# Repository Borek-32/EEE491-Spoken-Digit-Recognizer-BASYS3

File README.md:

# FPGA MFCC digit recognizer

This repository is the source-and-evidence release of an EEE491 fixed-point
spoken-digit recognizer for the Digilent Basys 3. The design acquires an
external ADC stream and implements the full feature/classification path in
VHDL:

```text
ADC/VAD -> Hann window -> 512-point FFT -> 32-channel Mel bank
        -> log2 approximation -> 8-coefficient DCT -> template comparator
```

The packaged hardware profile is the home-fabricated microphone/ADC board on
Pmod JC. `constraints/jc_homefab.xdc` is the only top-level constraint file in
the release. Generated Vivado projects, checkpoints, bitstreams, logs and
waveform databases are deliberately not versioned.

## What is here

- `rtl/`: the eleven synthesizable VHDL units, with `top_module` as top.
- `testbench/` and `verification/`: eleven VHDL benches, retained fixed-point
  inputs/outputs, MATLAB cross-checks, and a bounded safe regression runner.
- `ip/` and `data/`: twenty AMD IP configuration files and five ROM
  initialization sources. Generated IP products are intentionally absent.
- `constraints/jc_homefab.xdc`: the complete 39-port Basys 3/JC pin profile.
- `hardware/homefab_mic_adc_pcb/`: KiCad sources, photos, verification tools,
  and report figures for the physical microphone/ADC board.
- `hardware/pcb_adc_uart/`: the isolated ADC-to-UART diagnostic and its
  explicitly bounded evidence.
- `implementation/`: retained text reports from the historical main
  run and the final JC-mapped implementation. These reports are evidence, not
  inputs to the clean build.
- `docs/report/EEE491_MFCC_Final_Report_2026-08-20.pdf`: the final project
  report.

## Quick start

Vivado 2025.2 is the reference version. Choose fresh directories outside this
repository; the scripts reject in-tree or pre-existing output directories.
Run Vivado itself from a fresh external runtime directory so journals, logs and
`.Xil` process state never enter the checkout.

```bash
repo_root=$(pwd -P)
build_dir=$(readlink -m ../mfcc-build-v1.0.0)
results_dir=$(readlink -m ../mfcc-results-v1.0.0)
runtime_dir=$(readlink -m ../mfcc-runtime-v1.0.0)
mkdir -- "$runtime_dir"

(
  cd "$runtime_dir"
  vivado -mode batch -notrace \
    -journal "$runtime_dir/01-recreate.jou" \
    -log "$runtime_dir/01-recreate.log" \
    -source "$repo_root/scripts/recreate_project.tcl" \
    -tclargs "$build_dir"

  vivado -mode batch -notrace \
    -journal "$runtime_dir/04-build-jc.jou" \
    -log "$runtime_dir/04-build-jc.log" \
    -source "$repo_root/scripts/build_jc_homefab.tcl" \
    -tclargs "$build_dir" "$results_dir" 4
)
```

The first command copies the release inputs into the external build directory,
creates a new project for `xc7a35tcpg236-1`, and regenerates IP products there.
The second runs synthesis and implementation, validates timing/routing/DRC and
the complete package-pin map, then places reports and a generated bitstream in
the external results directory.

Run the repository integrity and privacy gate with:

```bash
python3 scripts/check_release.py
```

The gate also requires Git's clean-filtered bytes to match the worktree bytes,
so a commit and fresh checkout cannot silently invalidate `SHA256SUMS`.

Or run the complete non-hardware release workflow in fresh external directories:

```bash
scripts/run_release_checks.sh ../mfcc-build-v1.0.0 \
  ../mfcc-results-v1.0.0 --top-smoke --jobs 4
```

`VIVADO_BIN` and `MATLAB_BIN` may name alternate executables. The wrapper runs
the integrity gate, recreation, nine safe XSim benches, optional top smoke,
MATLAB gates, and the full JC build. It creates the fresh external
`../mfcc-results-v1.0.0.runtime/` directory for Vivado process state and never
programs hardware. The MATLAB gate is serialized and refuses to start while
another MATLAB process is active.

See [REPRODUCIBILITY.md](REPRODUCIBILITY.md) for simulation, MATLAB, KiCad and
hardware procedures.

## Verified result and evidence boundary

The retained final JC implementation reports:

- routed setup slack `+0.671 ns` and hold slack `+0.020 ns`;
- 12,824/12,824 routable nets complete, with zero routing errors;
- zero DRC errors, critical warnings, or warnings (11 advisories);
- 5,603 LUTs, 8,437 registers, 23.5 BRAM tiles, and 15 DSPs.

Those are internal FPGA implementation results. The methodology report retains
36 `TIMING-18` warnings because external I/O delays were not characterized;
the ADC board interface is therefore not claimed as board-level timing closed.

The report describes a working bench demonstration and historical recognition
observations. No pre-labeled live session made with the final FFT/Mel-corrected
image was retained, so this release makes no numerical live-accuracy claim.
The earlier 30/30 development set predates those final corrections and is not
presented as final-system accuracy. Photographs show construction and operation;
they do not independently establish recognition accuracy.

The isolated ADC/UART reconstruction closes its declared internal timing, but
its retained CDC report contains 133 `CDC-1` critical findings, 12 `CDC-15`
warnings, and four `CDC-3` informational findings. Its corrected SPI-alignment
candidate passes simulation and implementation; the decisive voltage/UART
endpoint capture remains **NOT RUN**. These boundaries are preserved in the
corresponding hardware documentation.

## Hardware safety and explicit target selection

No script selects a programmer or serial port by a repository-embedded device
identifier. Programming requires both an explicit bitstream path and an
explicit JTAG target substring and the expected bitstream SHA-256. MATLAB
capture requires an explicit UART port, JTAG target identity, bitstream path,
expected SHA-256, programming-log path, and output path.
Inspect the discovered target and wiring before acting; a generated bitstream
or a successful JTAG configuration is not proof of correct analog behavior.

## License and citation

Original source and hardware-design files are released under the MIT License;
portfolio media, the report, retained evidence, and third-party tool/IP
material have the narrower terms described in [NOTICE.md](NOTICE.md). Citation
metadata is in [CITATION.cff](CITATION.cff).

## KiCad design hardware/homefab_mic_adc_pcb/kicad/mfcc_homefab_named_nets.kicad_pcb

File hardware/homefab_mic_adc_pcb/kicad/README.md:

# Reconciled KiCad source

This directory contains the report-ready schematic and the recovered PCB with
every routed copper island assigned its schematic net name; the one physically
isolated, unused Pmod pad is explicitly retained as `<no net>`.

- `mfcc_homefab_named_nets.kicad_sch`: schematic with the ADC ground joined to
  the existing global `GND` net.
- `mfcc_homefab_named_nets.kicad_pcb`: original board geometry with net names
  added to all pads, routed segments, and vias.
- `mfcc_homefab_named_nets.kicad_pro`: KiCad project settings generated for the
  reconciled pair.
- `tools/`: fail-closed reconstruction and verification scripts.
- `evidence/`: exported netlist, IPC-D-356 netlist, native KiCad checks,
  hashes, and the inspected schematic render.

The pre-reconciliation source copies are retained under `originals/`. Their
SHA-256 values are:

- schematic: `e35c51a3030d64c75fbf8b99cae6bb0e8106192cca6c8ed2968b3d3029f0215c`
- PCB: `d63a80d06c6ad783caed415275df6e86c6c870cf5f2c0cff97cd489689012f88`

## Exact net reconciliation

KiCad 10.0.3 native connectivity found 22 physical copper islands. Twenty-one
use the exact exported schematic names; the remaining island is an intentionally
isolated Pmod pad and remains `<no net>`.

| Island | Exact net | Pads | Segments | Vias |
| --- | --- | ---: | ---: | ---: |
| I001 | `/ref` | 4 | 12 | 0 |
| I002 | `/3v3` | 4 | 26 | 3 |
| I003 | `/JC9` | 2 | 33 | 4 |
| I004 | `GND` | 12 | 50 | 3 |
| I005 | `<no net>` | 1 | 0 | 0 |
| I006 | `/JC4` | 3 | 9 | 2 |
| I007 | `VCC` | 5 | 33 | 2 |
| I008 | `/JC3` | 2 | 4 | 1 |
| I009 | `/filter-out` | 4 | 13 | 1 |
| I010 | `/div-ref` | 4 | 14 | 0 |
| I011 | `/mic` | 3 | 15 | 2 |
| I012 | `/ss2r` | 3 | 6 | 0 |
| I013 | `/div-out` | 3 | 8 | 0 |
| I014 | `/ss2c` | 3 | 8 | 0 |
| I015 | `/amp1` | 3 | 10 | 0 |
| I016 | `/pot1` | 2 | 6 | 0 |
| I017 | `/ss1c` | 3 | 8 | 0 |
| I018 | `/ss1o` | 4 | 10 | 0 |
| I019 | `/amp2` | 2 | 7 | 0 |
| I020 | `/amp-out` | 3 | 4 | 0 |
| I021 | `/ss1r` | 3 | 8 | 0 |
| I022 | `/pot2` | 2 | 3 | 0 |

The exported schematic contains exactly these 21 named nets, and the named PCB
contains the same 21-name set. Coverage is complete: 75 pads, 287 track
segments, and 18 vias are accounted for. The before/after structured geometry
fingerprints are identical.

## Home-fabrication mirror

The successful physical board is mirrored relative to the logical pad numbers
in the recovered footprints. Net assignment therefore follows the working
electrical pins, not the printed geometric pad numbers.

ADC footprint geometry maps to the
[TI ADC121S101 pinout](https://www.ti.com/lit/ds/symlink/adc121s101.pdf)
as follows:

| Geometric pad | Actual ADC pin/function | Net |
| ---: | --- | --- |
| 1 | 3, `VIN` | `/ref` |
| 2 | 2, `GND` | `GND` |
| 3 | 1, `VA` | `/3v3` |
| 4 | 6, `/CS` | `/JC9` |
| 5 | 5, `SDATA` | `/JC4` |
| 6 | 4, `SCLK` | `/JC3` |

For the SO-14 LM324, the actual lead is `15 - geometric pad`. This places the
actual positive supply on geometric pad 11 (`VCC`) and the actual negative
supply on geometric pad 4 (`GND`), and it resolves all four amplifier stages.
The two recovered board diode references are also reversed by role relative to
the schematic; the net assignment follows the electrical clamp nodes.

## Ground correction

The source schematic used both the global `GND` net and a local `/gnd` label
for the ADC. The fabricated PCB has one common ground island. The reconciled
schematic therefore replaces only that local label with a wired global GND
symbol. It now exports one `GND` net and no `/gnd` or anonymous ADC-ground net.

## Verification boundary

`evidence/bundle_validation.json` records `PASS_NET_ASSIGNMENT`:

- 21/21 schematic names equal 21/21 named PCB nets;
- all pads, tracks, and vias are assigned to their native KiCad island;
- one isolated Pmod pad is deliberately left no-net;
- no board geometry changed;
- KiCad DRC reports zero unconnected items.

This does **not** make the legacy home-fabrication layout DRC-clean. The retained
DRC contains 126 inherited findings: 12 errors and 114 warnings, including two
copper-clearance findings, malformed/co-located Pmod holes, courtyard overlaps,
a missing formal `Edge.Cuts` outline, and dangling legacy stubs. The schematic
ERC retains 28 pre-existing structural findings (8 errors and 20 warnings),
principally because the drawing models four op-amp triangles as separate
references rather than one multi-unit LM324 package and omits connector/power
driver detail. These limitations are preserved rather than hidden.

The direct Pmod footprint also joins the geometric contacts corresponding to
JC4 and JC10. The full FPGA design still drives JC10 as a separate `pmod`
output, so that contact must remain physically unpopulated/isolated or the FPGA
constraint must be disabled before treating a future revision as fab-ready.

## Reproduce the checks

Run the net assignment with KiCad's Python runtime:

```bash
flatpak run --command=python3 org.kicad.KiCad \
  tools/assign_schematic_nets.py SOURCE.kicad_pcb OUTPUT.kicad_pcb \
  --manifest evidence/net_assignment_manifest.json
```

Then export the schematic netlist/ERC and PCB DRC with `kicad-cli`, and run:

```bash
python3 tools/verify_named_bundle.py . \
  --desktop-schematic originals/mfcc.kicad_sch \
  --desktop-board originals/mfccsmd.kicad_pcb \
  --output evidence/bundle_validation.json
```

`PASS_NET_ASSIGNMENT` is deliberately narrower than fabrication approval. The
retained 126 PCB DRC and 28 schematic ERC findings remain open. Machine-local
paths in the exported evidence were replaced with repository-relative names;
the visible `borek32` copper marking is retained as intentional attribution.

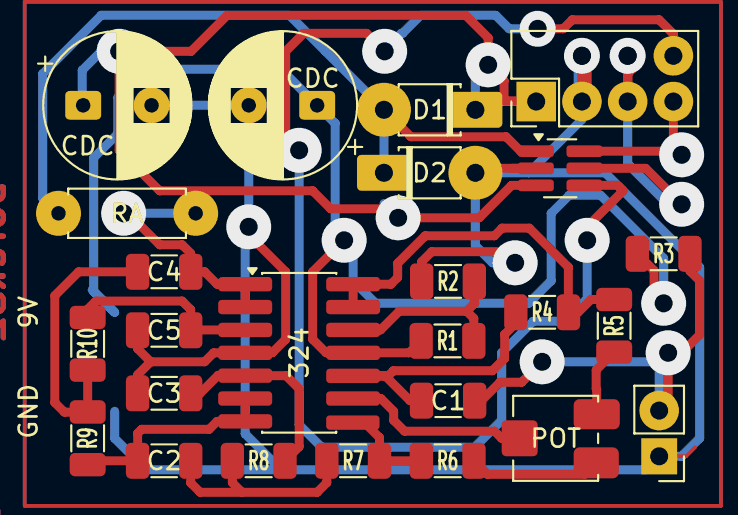
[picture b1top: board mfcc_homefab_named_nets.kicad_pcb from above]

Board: 2 copper layers, 24 parts (0 on the bottom side), 18 nets.

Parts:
9V: SolderWirePad_1x01_SMD_4x8mm
324: SO-14_3.9x8.65mm_P1.27mm
C1, C2, C3, C4, C5: C_1206_3216Metric
CDC: CP_Radial_D8.0mm_P3.80mm
CDC#2: CP_Radial_D8.0mm_P3.80mm
D1, D2: D_T-1_P5.08mm_Horizontal
GND: SolderWirePad_1x01_SMD_4x8mm
POT: Potentiometer_Bourns_3314J_Vertical
R1, R2, R3, R4, R5, R6, R7, R8, R9, R10: R_1206_3216Metric
RA: R_Axial_DIN0207_L6.3mm_D2.5mm_P7.62mm_Horizontal

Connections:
/3v3: CDC#2.1, D1.1
/amp1: 324.10, C1.1, R4.1
/amp2: 324.9, POT.2
/amp-out: 324.8, R6.1, R7.2
/div-out: 324.12, R1.1, R2.2
/div-ref: 324.13, 324.14, R4.2, R5.1
/filter-out: 324.1, 324.2, C4.2, RA.1
/mic: C1.2, R3.1
/pot1: POT.3, R5.2
/pot2: POT.1, R6.2
/ref: D1.2, D2.1, RA.2
/ss1c: 324.5, C3.1, R8.2
/ss1o: 324.6, 324.7, C2.1, R9.1
/ss1r: C2.2, R7.1, R8.1
/ss2c: 324.3, C5.2, R10.2
/ss2r: C4.1, R9.2, R10.1
GND: 324.4, C3.2, C5.1, CDC.2, CDC#2.2, D2.2, GND.1, R2.1
VCC: 9V.1, 324.11, CDC.1, R1.2, R3.2
